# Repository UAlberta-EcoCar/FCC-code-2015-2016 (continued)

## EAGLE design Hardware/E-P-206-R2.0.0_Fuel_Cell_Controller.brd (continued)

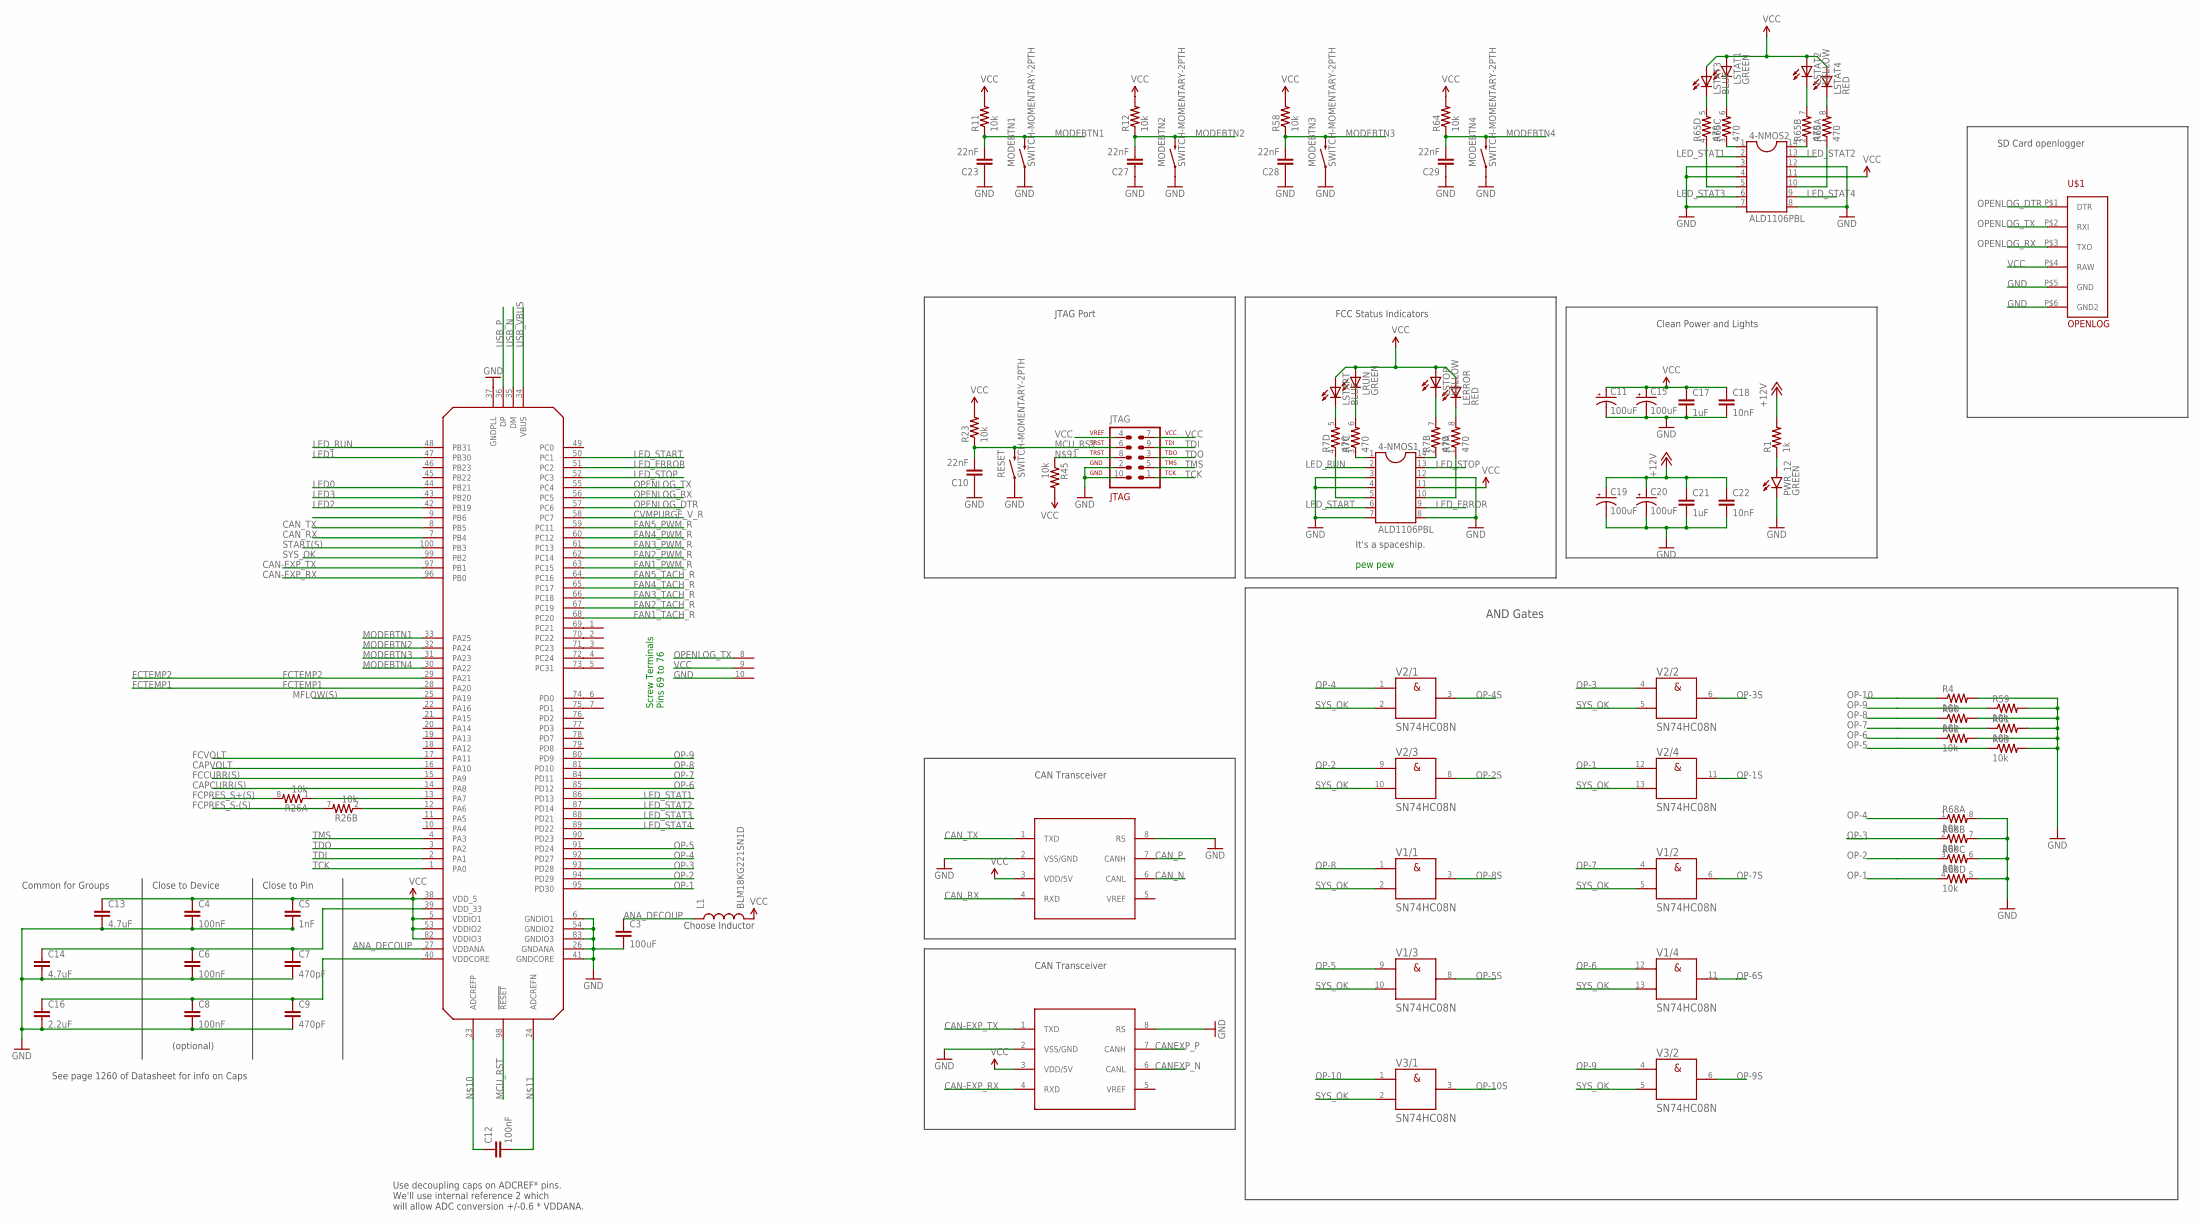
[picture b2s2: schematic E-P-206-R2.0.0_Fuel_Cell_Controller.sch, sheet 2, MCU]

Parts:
4-NMOS1, 4-NMOS2: ALD1106PBL; SOIC-14
C3: 100uF; 0805
C4, C6, C8: 100nF; 0603-CAP
C5: 1nF; 0603-CAP
C7, C9: 470pF; 0603-CAP
C10, C23, C27, C28, C29: 22nF; 0603-CAP
C11, C15, C19, C20: 100uF; PANASONIC_C
C12: 100nF; 0805
C13, C14: 4.7uF; 0805
C16: 2.2uF; 0805
C17, C21: 1uF; 0805
C18, C22: 10nF; 0603-CAP
JTAG: 2x5; AVR-JTAG-10
L1: BLM18KG221SN1D; 0603
LERROR: RED; LED-1206
LRUN: GREEN; LED-1206
LSTART: BLUE; LED-1206
LSTAT1: GREEN; LED-1206
LSTAT2: YELLOW; LED-1206
LSTAT3: BLUE; LED-1206
LSTAT4: RED; LED-1206
LSTOP: YELLOW; LED-1206
MCU: AT32UC3C1512; TQFP100
MODEBTN1, MODEBTN2, MODEBTN3, MODEBTN4: SWITCH-MOMENTARY-2PTH; TACTILE-PTH
PWR_12: GREEN; LED-1206
R1: 1k; 0603-RES
R4, R11, R12, R23, R45, R58, R59, R60, R61, R62, R63, R64: 10k; 0603-RES
R7, R65: 470; 0603-ARV
R26, R68: 10k; 0603-ARV
RESET: SWITCH-MOMENTARY-2PTH; TACTILE-PTH
U$1: OPENLOG
U$2: 10X1PCBBLOCK
U$4, U$36: MCP2551; 8-SOIC
V1, V2, V3: SN74HC08N; DIL14

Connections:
+12V: C19.+, C20.+, C21.1, C22.1, R1.2; also elsewhere on the board
+UB: V1.14 (+UB), V2.14 (+UB), V3.14 (+UB)
-UB: V1.7 (-UB), V2.7 (-UB), V3.7 (-UB)
ANA_DECOUP: C3.1, L1.1, MCU.27 (VDDANA)
CAN-EXP_RX: MCU.96 (PB0), U$36.4 (RXD)
CAN-EXP_TX: MCU.97 (PB1), U$36.1 (TXD)
CANEXP_N: U$36.6 (CANL)
CANEXP_P: U$36.7 (CANH)
CAN_N: U$4.6 (CANL)
CAN_P: U$4.7 (CANH)
CAN_RX: MCU.7 (PB4), U$4.4 (RXD)
CAN_TX: MCU.8 (PB5), U$4.1 (TXD)
CAPCURR(S): MCU.14 (PA8); also elsewhere on the board
CAPVOLT: MCU.16 (PA10); also elsewhere on the board
CVMPURGE_V_R: MCU.58 (PC7); also elsewhere on the board
FAN1_PWM_R: MCU.63 (PC15); also elsewhere on the board
FAN1_TACH_R: MCU.68 (PC20); also elsewhere on the board
FAN2_PWM_R: MCU.62 (PC14); also elsewhere on the board
FAN2_TACH_R: MCU.67 (PC19); also elsewhere on the board
FAN3_PWM_R: MCU.61 (PC13); also elsewhere on the board
FAN3_TACH_R: MCU.66 (PC18); also elsewhere on the board
FAN4_PWM_R: MCU.60 (PC12); also elsewhere on the board
FAN4_TACH_R: MCU.65 (PC17); also elsewhere on the board
FAN5_PWM_R: MCU.59 (PC11); also elsewhere on the board
FAN5_TACH_R: MCU.64 (PC16); also elsewhere on the board
FCCURR(S): MCU.15 (PA9); also elsewhere on the board
FCPRES_S+(S): R26.8 (2); also elsewhere on the board
FCPRES_S-(S): R26.7 (2); also elsewhere on the board
FCTEMP1: MCU.28 (PA20); also elsewhere on the board
FCTEMP2: MCU.29 (PA21); also elsewhere on the board
FCVOLT: MCU.17 (PA11); also elsewhere on the board
GND: 4-NMOS1.3, 4-NMOS1.4, 4-NMOS1.7, 4-NMOS1.8, 4-NMOS1.12, 4-NMOS2.8, 4-NMOS2.12, C3.2, C4.2, C5.2, C6.2, C7.2, C8.2, C9.2, C10.1, C11.-, C13.2, C14.2, C15.-, C16.2, C17.2, C18.2, C19.-, C20.-, C21.2, C22.2, C23.1, C27.1, C28.1, C29.1, JTAG.2, JTAG.10, MCU.6 (GNDIO1), MCU.26 (GNDANA), MCU.37 (GNDPLL), MCU.41 (GNDCORE), MCU.54 (GNDIO2), MCU.83 (GNDIO3), MODEBTN1.1, MODEBTN2.1, MODEBTN3.1, MODEBTN4.1, PWR_12.C, R4.2, R59.2, R60.2, R61.2, R62.2, R63.2, R68.5 (2), R68.6 (2), R68.7 (2), R68.8 (2), RESET.1, U$1.P$5 (GND), U$1.P$6 (GND2), U$2.10, U$4.2 (VSS/GND), U$4.8 (RS), U$36.2 (VSS/GND), U$36.8 (RS); also elsewhere on the board
LED0: MCU.44 (PB21); also elsewhere on the board
LED1: MCU.47 (PB30); also elsewhere on the board
LED2: MCU.42 (PB19); also elsewhere on the board
LED3: MCU.43 (PB20); also elsewhere on the board
LED_ERROR: 4-NMOS1.9, MCU.51 (PC2)
LED_RUN: 4-NMOS1.2, MCU.48 (PB31)
LED_START: 4-NMOS1.6, MCU.50 (PC1)
LED_STAT1: 4-NMOS2.2, MCU.86 (PD13)
LED_STAT2: 4-NMOS2.13, MCU.87 (PD14)
LED_STAT3: 4-NMOS2.3, 4-NMOS2.4, 4-NMOS2.6, 4-NMOS2.7, MCU.88 (PD21)
LED_STAT4: 4-NMOS2.9, MCU.89 (PD22)
LED_STOP: 4-NMOS1.13, MCU.52 (PC3)
MCU_RST: C10.2, JTAG.6, MCU.98 (!RESET), R23.1, RESET.3 (2); also elsewhere on the board
MFLOW(S): MCU.25 (PA19); also elsewhere on the board
MODEBTN1: C23.2, MCU.33 (PA25), MODEBTN1.3 (2), R11.1
MODEBTN2: C27.2, MCU.32 (PA24), MODEBTN2.3 (2), R12.1
MODEBTN3: C28.2, MCU.31 (PA23), MODEBTN3.3 (2), R58.1
MODEBTN4: C29.2, MCU.30 (PA22), MODEBTN4.3 (2), R64.1
unnamed: MCU.12 (PA6), R26.2 (1)
unnamed: MCU.13 (PA7), R26.1
unnamed: C6.1, C7.1, C14.1, MCU.39 (VDD_33)
unnamed: C8.1, C9.1, C16.1, MCU.40 (VDDCORE)
unnamed: C12.1, MCU.23 (ADCREFP)
unnamed: C12.2, MCU.24 (ADCREFN)
unnamed: MCU.69 (PC21), U$2.1
unnamed: MCU.70 (PC22), U$2.2
unnamed: MCU.71 (PC23), U$2.3
unnamed: LSTART.C, R7.5 (2)
unnamed: LRUN.C, R7.6 (2)
unnamed: MCU.72 (PC24), U$2.4
unnamed: MCU.73 (PC31), U$2.5
unnamed: 4-NMOS1.5, R7.4 (1)
unnamed: 4-NMOS1.1, R7.3 (1)
unnamed: PWR_12.A, R1.1
unnamed: MCU.74 (PD0), U$2.6
unnamed: MCU.75 (PD1), U$2.7
unnamed: 4-NMOS2.5, R65.4 (1)
unnamed: 4-NMOS2.1, R65.3 (1)
unnamed: 4-NMOS2.14, R65.2 (1)
unnamed: 4-NMOS2.10, R65.1
unnamed: LSTAT3.C, R65.5 (2)
unnamed: 4-NMOS1.14, R7.2 (1)
unnamed: 4-NMOS1.10, R7.1
unnamed: LSTOP.C, R7.7 (2)
unnamed: LERROR.C, R7.8 (2)
unnamed: LSTAT1.C, R65.6 (2)
unnamed: LSTAT2.C, R65.7 (2)
unnamed: LSTAT4.C, R65.8 (2)
unnamed: JTAG.8, R45.1
OP-1: MCU.95 (PD30), R68.4 (1), V2.12 (A)
OP-1S: V2.11 (Y); also elsewhere on the board
OP-2: MCU.94 (PD29), R68.3 (1), V2.9 (A)
OP-2S: V2.8 (Y); also elsewhere on the board
OP-3: MCU.93 (PD28), R68.2 (1), V2.4 (A)
OP-3S: V2.6 (Y); also elsewhere on the board
OP-4: MCU.92 (PD27), R68.1, V2.1 (A)
OP-4S: V2.3 (Y); also elsewhere on the board
OP-5: MCU.91 (PD24), R63.1, V1.9 (A)
OP-5S: V1.8 (Y); also elsewhere on the board
OP-6: MCU.85 (PD12), R62.1, V1.12 (A)
OP-6S: V1.11 (Y); also elsewhere on the board
OP-7: MCU.84 (PD11), R61.1, V1.4 (A)
OP-7S: V1.6 (Y); also elsewhere on the board
OP-8: MCU.81 (PD10), R60.1, V1.1 (A)
OP-8S: V1.3 (Y); also elsewhere on the board
OP-9: MCU.80 (PD9), R59.1, V3.4 (A)
OP-9S: V3.6 (Y); also elsewhere on the board
OP-10: R4.1, V3.1 (A)
OP-10S: V3.3 (Y); also elsewhere on the board
OPENLOG_DTR: MCU.57 (PC6), U$1.P$1 (DTR)
OPENLOG_RX: MCU.56 (PC5), U$1.P$3 (TXO)
OPENLOG_TX: MCU.55 (PC4), U$1.P$2 (RXI), U$2.8
START(S): MCU.100 (PB3); also elsewhere on the board
SYS_OK: MCU.99 (PB2), V1.2 (B), V1.5 (B), V1.10 (B), V1.13 (B), V2.2 (B), V2.5 (B), V2.10 (B), V2.13 (B), V3.2 (B), V3.5 (B); also elsewhere on the board
TCK: JTAG.1, MCU.1 (PA0)
TDI: JTAG.9, MCU.2 (PA1)
TDO: JTAG.3, MCU.3 (PA2)
TMS: JTAG.5, MCU.4 (PA3)
USB_N: MCU.35 (DM)
USB_P: MCU.36 (DP)
USB_VBUS: MCU.34 (VBUS)
VCC: 4-NMOS1.11, 4-NMOS2.11, C4.1, C5.1, C11.+, C13.1, C15.+, C17.1, C18.1, JTAG.4, JTAG.7, L1.2, LERROR.A, LRUN.A, LSTART.A, LSTAT1.A, LSTAT2.A, LSTAT3.A, LSTAT4.A, LSTOP.A, MCU.5 (VDDIO1), MCU.38 (VDD_5), MCU.53 (VDDIO2), MCU.82 (VDDIO3), R11.2, R12.2, R23.2, R45.2, R58.2, R64.2, U$1.P$4 (RAW), U$2.9, U$4.3 (VDD/5V), U$36.3 (VDD/5V); also elsewhere on the board

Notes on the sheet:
Choose Inductor
Use decoupling caps on ADCREF* pins. We'll use internal reference 2 which will allow ADC conversion +/-0.6 * VDDANA.
Close to Pin
Close to Device
Common for Groups
JTAG Port
(optional)
See page 1260 of Datasheet for info on Caps
CAN Transceiver
Clean Power and Lights
FCC Status Indicators
It's a spaceship.
pew pew
AND Gates
Screw Terminals Pins 69 to 76
SD Card openlogger

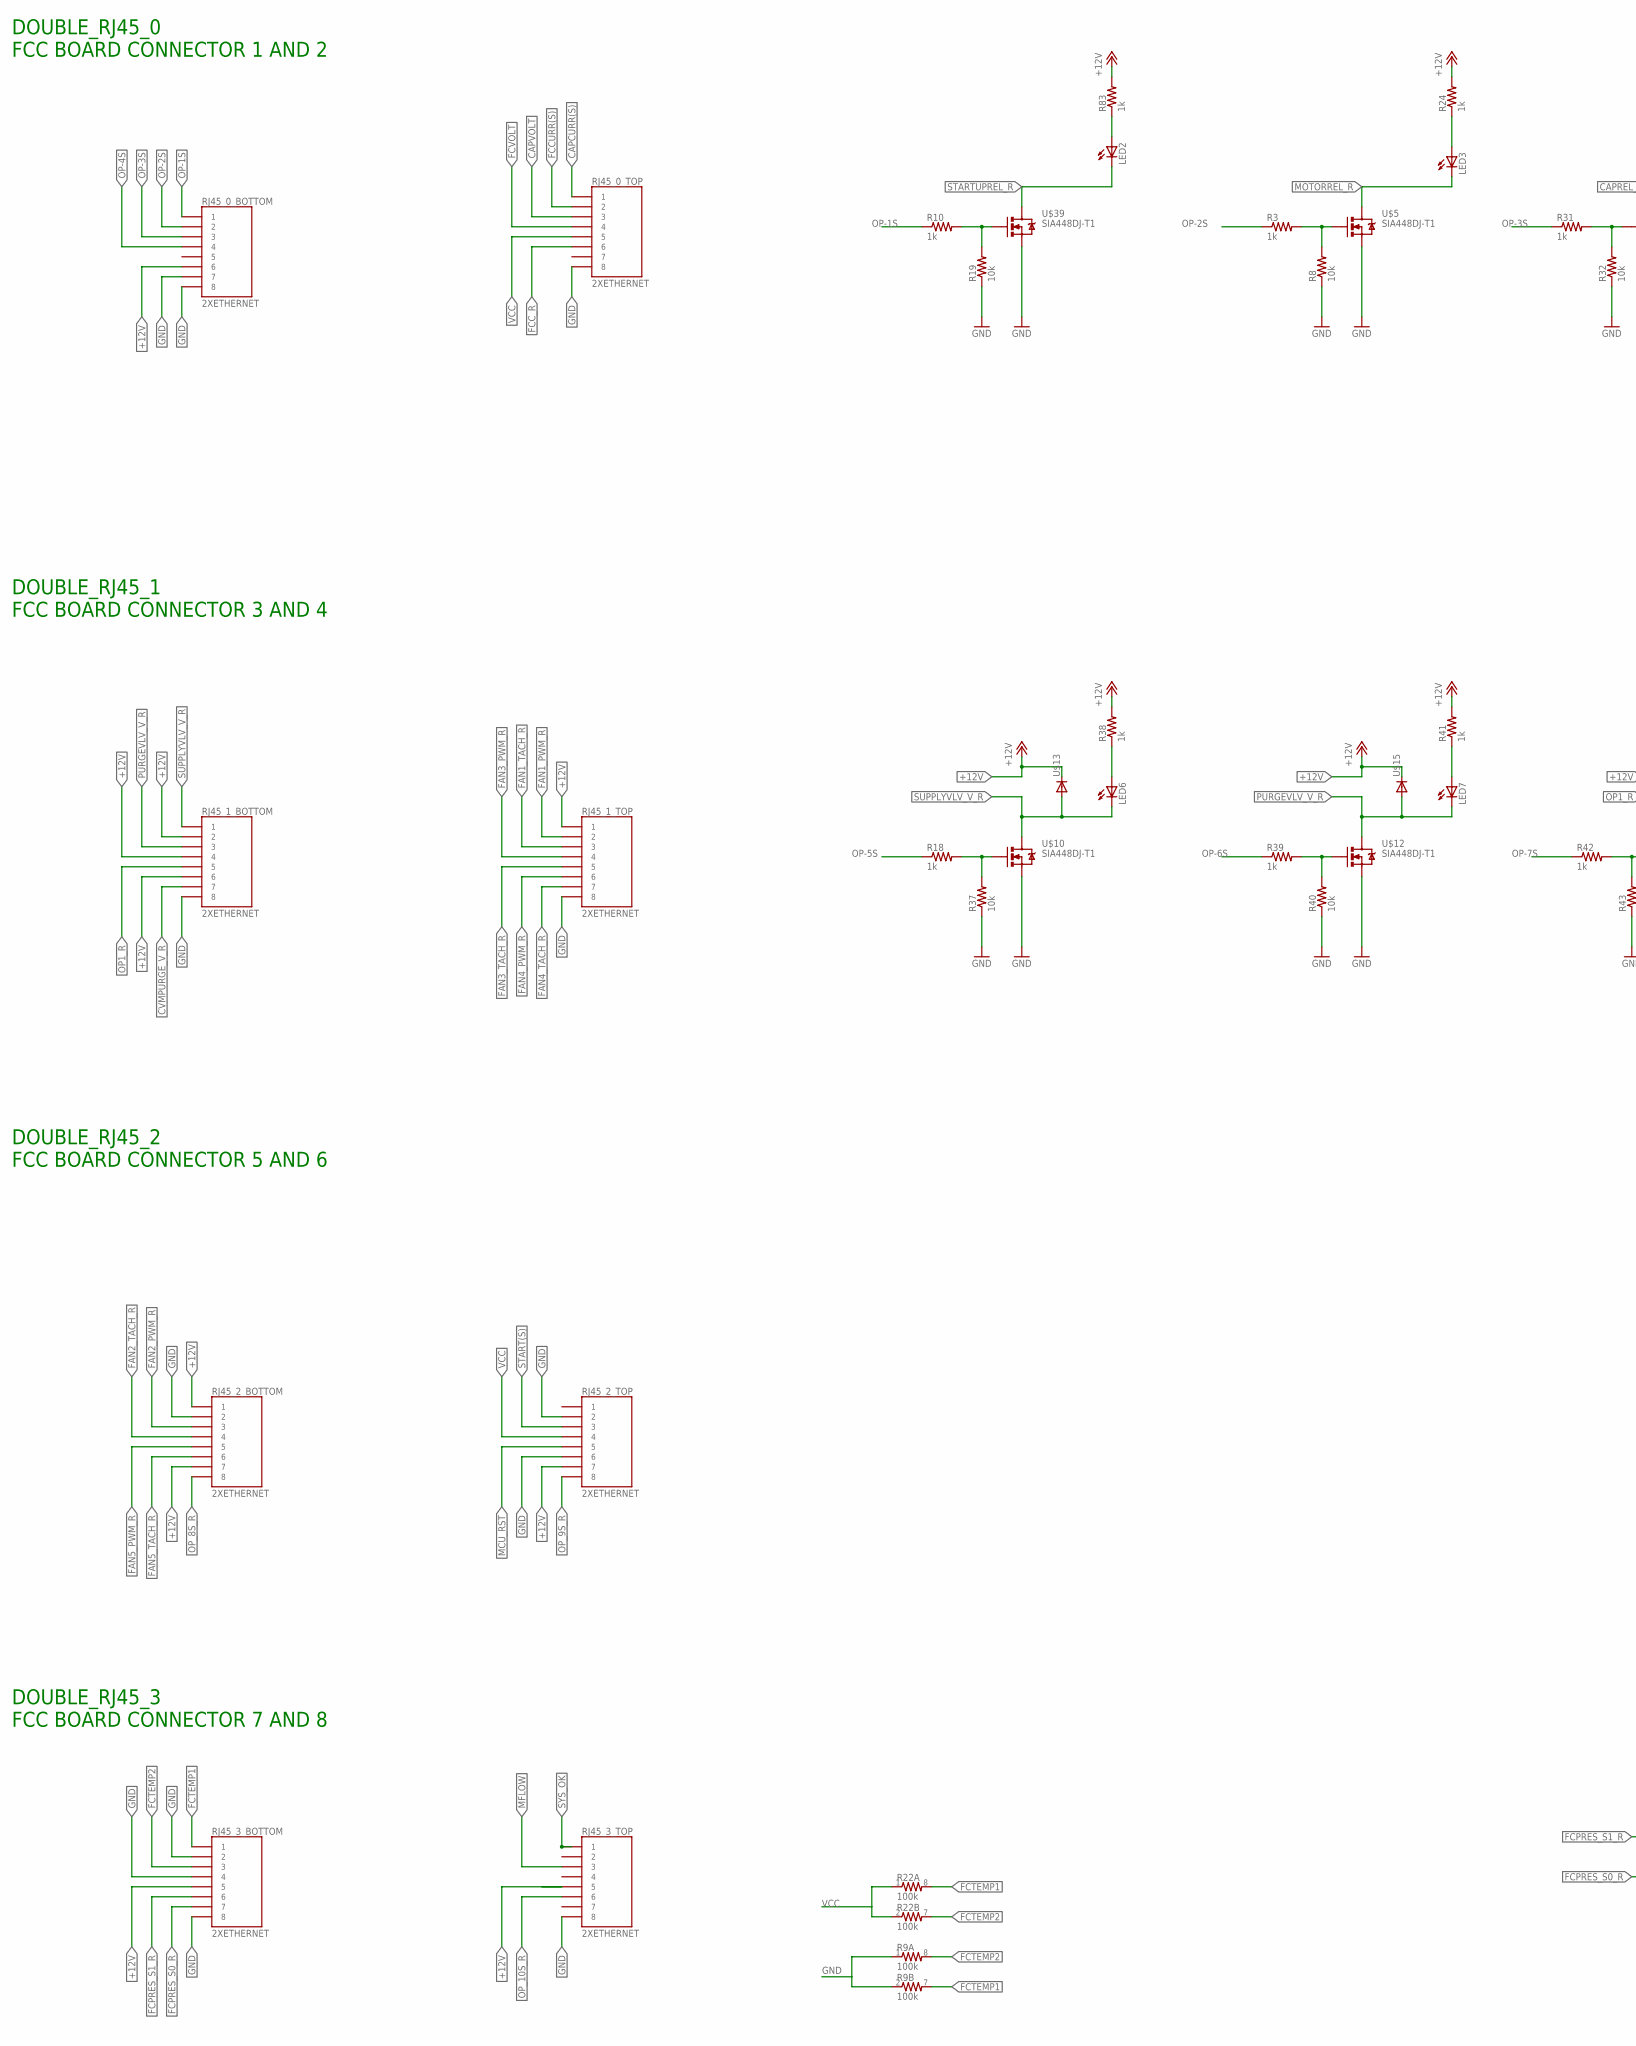
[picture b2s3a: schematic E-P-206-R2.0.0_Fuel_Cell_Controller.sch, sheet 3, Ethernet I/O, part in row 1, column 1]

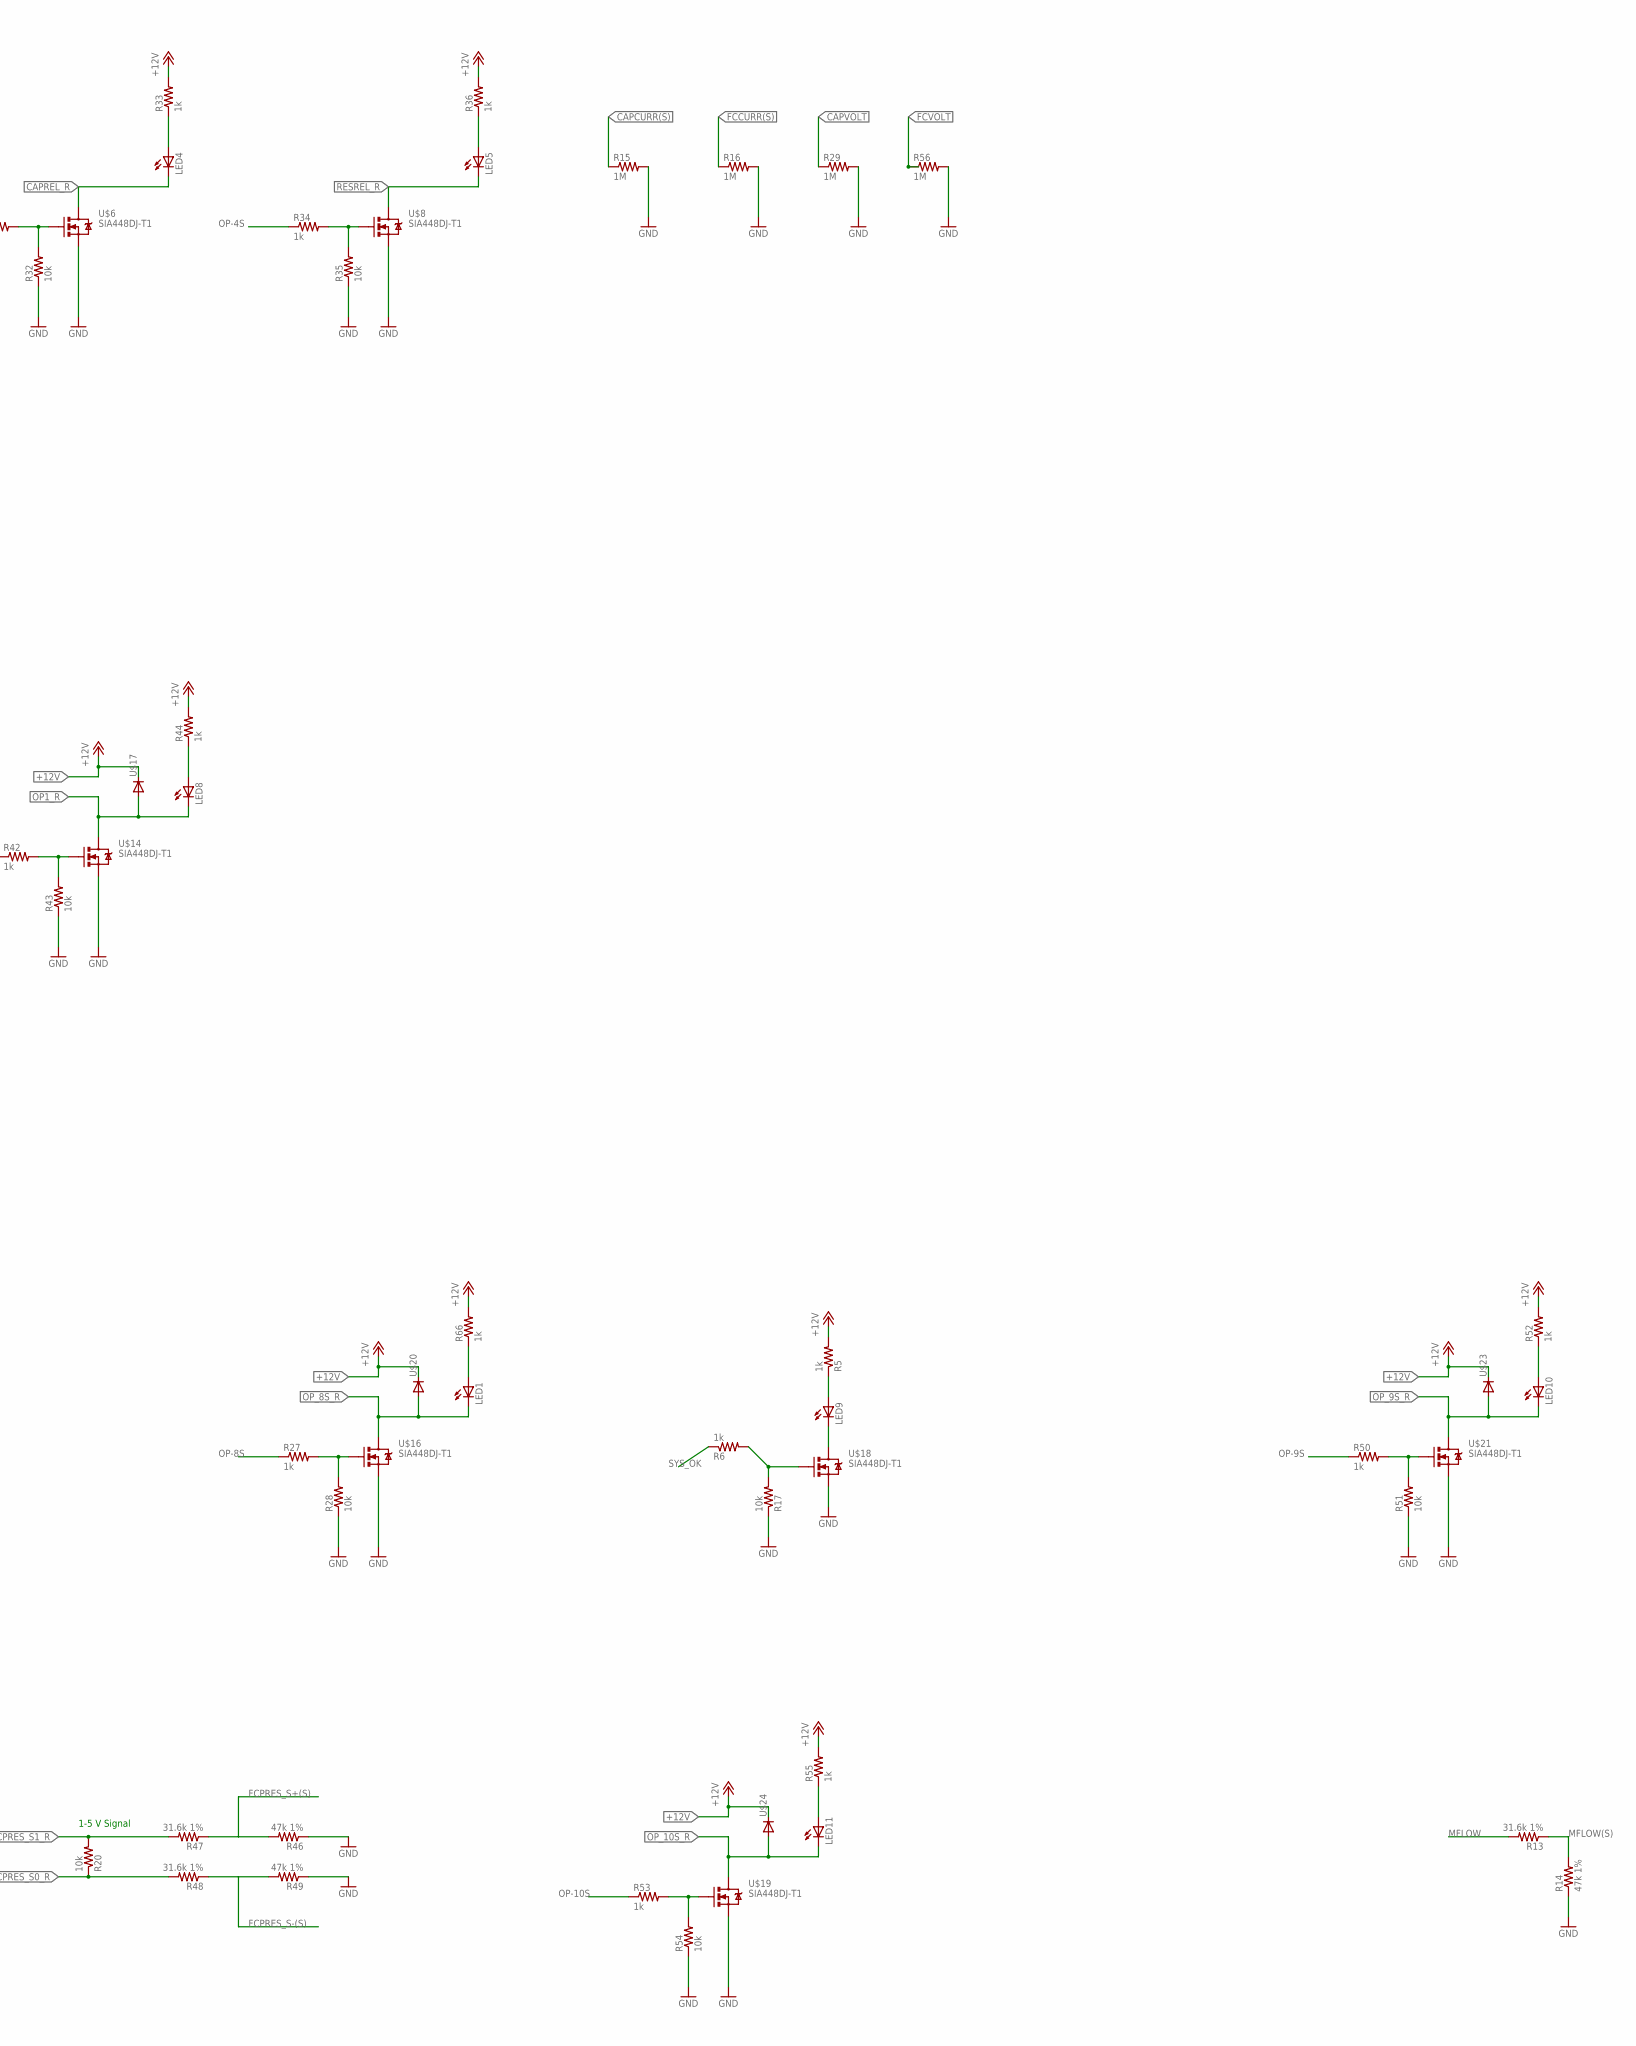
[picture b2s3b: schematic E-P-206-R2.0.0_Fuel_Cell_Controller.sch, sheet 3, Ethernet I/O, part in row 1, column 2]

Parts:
LED1, LED2, LED3, LED4, LED5, LED6, LED7, LED8, LED9, LED10, LED11: LED1206; LED-1206
R3, R5, R6, R10, R18, R24, R27, R31, R33, R34, R36, R38, R39, R41, R42, R44, R50, R52, R53, R55, R66, R83: 1k; 0603-RES
R8, R17, R19, R20, R28, R32, R35, R37, R40, R43, R51, R54: 10k; 0603-RES
R9, R22: 100k; 0603-ARV
R13, R47, R48: 31.6k 1%; 0603-RES
R14, R46, R49: 47k 1%; 0603-RES
R15, R16, R29, R56: 1M; R0805
RJ45_0_, RJ45_1_, RJ45_2_, RJ45_3_: 2XETHERNET
U$5, U$6, U$8, U$10, U$12, U$14, U$16, U$18, U$19, U$21, U$39: SIA448DJ-T1; SC70-6L
U$13, U$15, U$17, U$20, U$23, U$24: DIODE-DO214AC; DO214AC

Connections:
+12V: R5.2, R24.2, R33.2, R36.2, R38.2, R41.2, R44.2, R52.2, R55.2, R66.2, R83.2, RJ45_0_.B_6 (6), RJ45_1_.B_2 (2), RJ45_1_.B_4 (4), RJ45_1_.B_6 (6), RJ45_1_.T_1 (1), RJ45_2_.B_1 (1), RJ45_2_.B_7 (7), RJ45_2_.T_7 (7), RJ45_3_.B_5 (5), RJ45_3_.T_5 (5), U$13.C, U$15.C, U$17.C, U$20.C, U$23.C, U$24.C; also elsewhere on the board
CAPCURR(S): R15.1, RJ45_0_.T_1 (1); also elsewhere on the board
CAPREL_R: LED4.C, U$6.D
CAPVOLT: R29.1, RJ45_0_.T_3 (3); also elsewhere on the board
CVMPURGE_V_R: RJ45_1_.B_7 (7); also elsewhere on the board
FAN1_PWM_R: RJ45_1_.T_2 (2); also elsewhere on the board
FAN1_TACH_R: RJ45_1_.T_3 (3); also elsewhere on the board
FAN2_PWM_R: RJ45_2_.B_3 (3); also elsewhere on the board
FAN2_TACH_R: RJ45_2_.B_4 (4); also elsewhere on the board
FAN3_PWM_R: RJ45_1_.T_4 (4); also elsewhere on the board
FAN3_TACH_R: RJ45_1_.T_5 (5); also elsewhere on the board
FAN4_PWM_R: RJ45_1_.T_6 (6); also elsewhere on the board
FAN4_TACH_R: RJ45_1_.T_7 (7); also elsewhere on the board
FAN5_PWM_R: RJ45_2_.B_5 (5); also elsewhere on the board
FAN5_TACH_R: RJ45_2_.B_6 (6); also elsewhere on the board
FCCURR(S): R16.1, RJ45_0_.T_2 (2); also elsewhere on the board
FCC_R: RJ45_0_.T_6 (6)
FCPRES_S0_R: R20.1, R48.2, RJ45_3_.B_7 (7)
FCPRES_S1_R: R20.2, R47.2, RJ45_3_.B_6 (6)
FCPRES_S+(S): R46.2, R47.1; also elsewhere on the board
FCPRES_S-(S): R48.1, R49.2; also elsewhere on the board
FCTEMP1: R9.7 (2), R22.8 (2), RJ45_3_.B_1 (1); also elsewhere on the board
FCTEMP2: R9.8 (2), R22.7 (2), RJ45_3_.B_3 (3); also elsewhere on the board
FCVOLT: R56.1, RJ45_0_.T_4 (4); also elsewhere on the board
GND: R8.1, R9.1, R9.2 (1), R14.1, R15.2, R16.2, R17.1, R19.1, R28.1, R29.2, R32.1, R35.1, R37.1, R40.1, R43.1, R46.1, R49.1, R51.1, R54.1, R56.2, RJ45_0_.B_7 (7), RJ45_0_.B_8 (8), RJ45_0_.T_8 (8), RJ45_1_.B_8 (8), RJ45_1_.T_8 (8), RJ45_2_.B_2 (2), RJ45_2_.T_2 (2), RJ45_2_.T_6 (6), RJ45_3_.B_2 (2), RJ45_3_.B_4 (4), RJ45_3_.B_8 (8), RJ45_3_.T_8 (8), U$5.S@0 (S), U$5.S@1 (S), U$6.S@0 (S), U$6.S@1 (S), U$8.S@0 (S), U$8.S@1 (S), U$10.S@0 (S), U$10.S@1 (S), U$12.S@0 (S), U$12.S@1 (S), U$14.S@0 (S), U$14.S@1 (S), U$16.S@0 (S), U$16.S@1 (S), U$18.S@0 (S), U$18.S@1 (S), U$19.S@0 (S), U$19.S@1 (S), U$21.S@0 (S), U$21.S@1 (S), U$39.S@0 (S), U$39.S@1 (S); also elsewhere on the board
MCU_RST: RJ45_2_.T_5 (5); also elsewhere on the board
MFLOW: R13.2, RJ45_3_.T_3 (3)
MFLOW(S): R13.1, R14.2; also elsewhere on the board
MOTORREL_R: LED3.C, U$5.D
unnamed: LED9.A, R5.1
unnamed: R10.2, R19.2, U$39.G
unnamed: LED9.C, U$18.D
unnamed: R3.2, R8.2, U$5.G
unnamed: LED2.A, R83.1
unnamed: R31.2, R32.2, U$6.G
unnamed: LED3.A, R24.1
unnamed: R34.2, R35.2, U$8.G
unnamed: LED4.A, R33.1
unnamed: R18.2, R37.2, U$10.G
unnamed: LED5.A, R36.1
unnamed: R27.2, R28.2, U$16.G
unnamed: R39.2, R40.2, U$12.G
unnamed: LED6.A, R38.1
unnamed: R42.2, R43.2, U$14.G
unnamed: LED7.A, R41.1
unnamed: R50.2, R51.2, U$21.G
unnamed: LED8.A, R44.1
unnamed: R53.2, R54.2, U$19.G
unnamed: R6.2, R17.2, U$18.G
unnamed: LED1.A, R66.1
unnamed: LED10.A, R52.1
unnamed: LED11.A, R55.1
OP1_R: LED8.C, RJ45_1_.B_5 (5), U$14.D, U$17.A
OP-1S: R10.1, RJ45_0_.B_1 (1); also elsewhere on the board
OP-2S: R3.1, RJ45_0_.B_2 (2); also elsewhere on the board
OP-3S: R31.1, RJ45_0_.B_3 (3); also elsewhere on the board
OP-4S: R34.1, RJ45_0_.B_4 (4); also elsewhere on the board
OP-5S: R18.1; also elsewhere on the board
OP-6S: R39.1; also elsewhere on the board
OP-7S: R42.1; also elsewhere on the board
OP-8S: R27.1; also elsewhere on the board
OP-9S: R50.1; also elsewhere on the board
OP-10S: R53.1; also elsewhere on the board
OP_8S_R: LED1.C, RJ45_2_.B_8 (8), U$16.D, U$20.A
OP_9S_R: LED10.C, RJ45_2_.T_8 (8), U$21.D, U$23.A
OP_10S_R: LED11.C, RJ45_3_.T_6 (6), U$19.D, U$24.A
PURGEVLV_V_R: LED7.C, RJ45_1_.B_3 (3), U$12.D, U$15.A
RESREL_R: LED5.C, U$8.D
START(S): RJ45_2_.T_3 (3); also elsewhere on the board
STARTUPREL_R: LED2.C, U$39.D
SUPPLYVLV_V_R: LED6.C, RJ45_1_.B_1 (1), U$10.D, U$13.A
SYS_OK: R6.1, RJ45_3_.T_1 (1); also elsewhere on the board
VCC: R22.1, R22.2 (1), RJ45_0_.T_5 (5), RJ45_2_.T_4 (4); also elsewhere on the board

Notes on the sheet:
DOUBLE_RJ45_0 FCC BOARD CONNECTOR 1 AND 2
DOUBLE_RJ45_1 FCC BOARD CONNECTOR 3 AND 4
DOUBLE_RJ45_2 FCC BOARD CONNECTOR 5 AND 6
DOUBLE_RJ45_3 FCC BOARD CONNECTOR 7 AND 8
1-5 V Signal

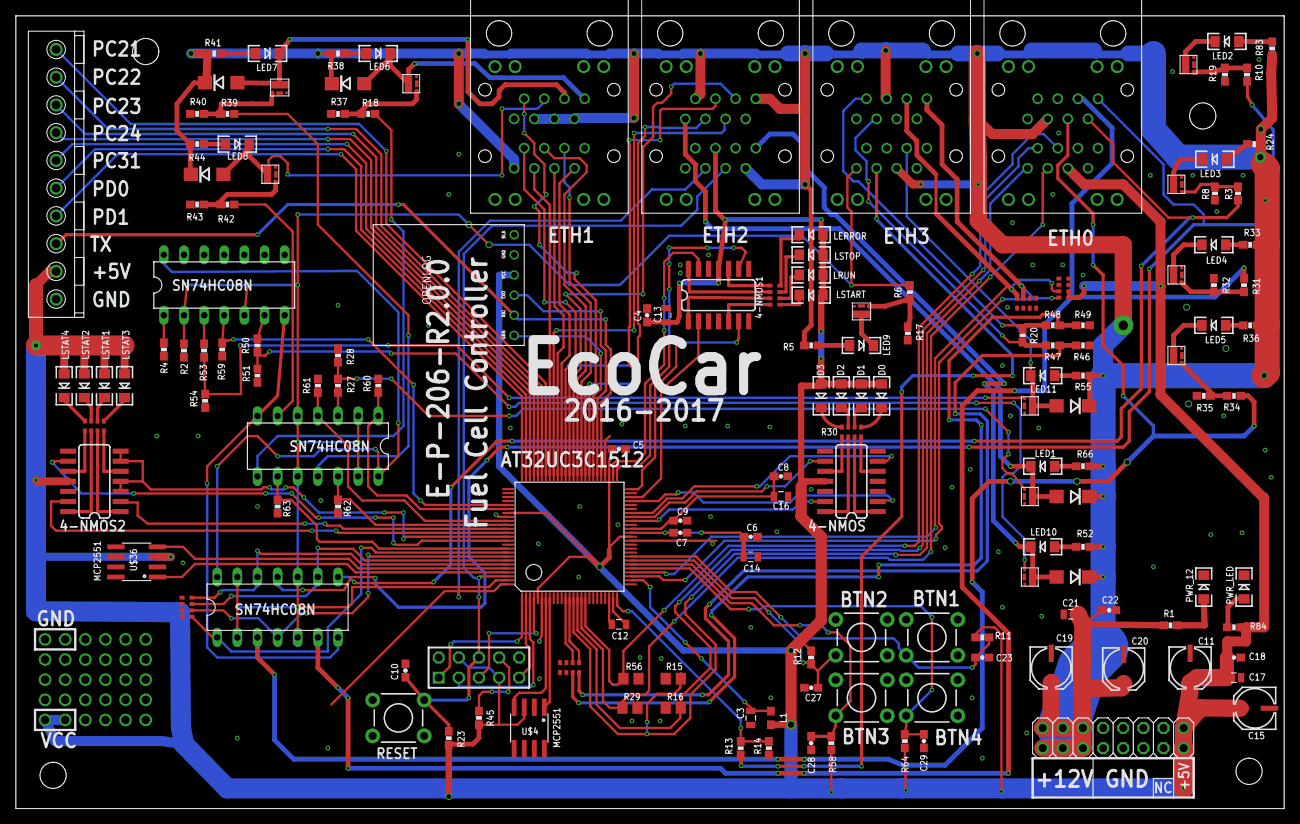
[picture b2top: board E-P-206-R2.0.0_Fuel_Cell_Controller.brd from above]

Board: 2 copper layers, 160.0 x 100.0 mm, 159 parts (0 on the bottom side), 152 nets.

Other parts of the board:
U$3, U$22, U$25, U$27: STAND-OFF

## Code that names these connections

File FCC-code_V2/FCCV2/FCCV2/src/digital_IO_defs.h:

/*
 * IncFile1.h
 *
 * Created: 2015-10-10 1:47:04 PM
 *  Author: Reegan
 */ 
#ifndef FUELCELL_IO_H
#define FUELCELL_IO_H
//digital Inputs
#define MODEBTN1 AVR32_PIN_PA25
#define MODEBTN2 AVR32_PIN_PA24
#define MODEBTN3 AVR32_PIN_PA23
#define MODEBTN4 AVR32_PIN_PA22
#define FAN5_TACH_R AVR32_PIN_PC16
#define CVM_PROBE_DISCONNECT AVR32_PIN_PC17
#define FAN3_TACH_R AVR32_PIN_PC18
#define FAN2_TACH_R AVR32_PIN_PC19
#define FAN1_TACH_R AVR32_PIN_PC20
#define CVM_PURGE_V_R AVR32_PIN_PC07
#define START AVR32_PIN_PB03
#define SYSOK AVR32_PIN_PB02
//PB23 unused
//PC00 unused
//PB22 unused
//PD02 unused
//PC06 unused
//LEDs
#define LED0 AVR32_PIN_PB21
#define LED1 AVR32_PIN_PB30
#define LED2 AVR32_PIN_PB19
#define LED3 AVR32_PIN_PB20
#define LED_RUN AVR32_PIN_PB31
#define LED_START AVR32_PIN_PC01
#define LED_ERROR AVR32_PIN_PC02
#define LED_STOP AVR32_PIN_PC03
#define LED_STAT1 AVR32_PIN_PD13
#define LED_STAT2 AVR32_PIN_PD14
#define LED_STAT3 AVR32_PIN_PD21
#define LED_STAT4 AVR32_PIN_PD22
//Coil driving outputs
#define OP_1 AVR32_PIN_PD30
#define OP_2 AVR32_PIN_PD29
#define OP_3 AVR32_PIN_PD28
#define OP_4 AVR32_PIN_PD27
#define OP_5 AVR32_PIN_PD24
#define OP_6 AVR32_PIN_PD12
#define OP_7 AVR32_PIN_PD11
#define OP_8 AVR32_PIN_PD10
#define OP_9 AVR32_PIN_PD09
//PD08 unused
//digital outputs
//relays
#define START_RELAY OP_1
#define RES_RELAY OP_4
#define CAP_RELAY OP_3
#define MOTOR_RELAY OP_2
//valves
#define PURGE_VALVE OP_6
#define H2_VALVE OP_5
#endif /* INCFILE1_H_ */

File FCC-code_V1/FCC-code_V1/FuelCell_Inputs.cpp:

#include "FuelCell_Inputs.h"
#include <avr32/io.h>
#include "myADC.h"

void InputsInit (void)
{
	//set DDR for all inputs
	//page 11 of datasheet needed
	
	
	//set analog inputs
	SetAsAnalogIn(1,5); //set PA5 as ADCIN1
	SetAsAnalogIn(1,7); //set PA7 as ADCIN3
	SetAsAnalogIn(1,8); //set PA8 as ADCIN4
	SetAsAnalogIn(1,9); //set PA9 as ADCIN5
	SetAsAnalogIn(1,10); //set PA10 as ADCIN6
	SetAsAnalogIn(1,11); //set PA11 as ADCIN7
	//maybe set up interrupts
	
	//set up ADC
	ADCInit();
}

unsigned char ReadSTART(void)
{
	//The START signal tiggers the Fuel Cell Controller
	//to go into its startup mode
	//Connected to PB3 = GPIO port 2 pin 3
	if(AVR32_GPIO.port[1].pvr & (1 << 3))
	{
		return(1);
	}
	return(0); 
}

unsigned char ReadSYSOK(void)
{
	//The SYSOK signal indicates that the system 
	//is in proper operating condition. 
	//It should be shorted to ground in case of an 
	//emergency stop event such as an emergency 
	//stop button press, or unsafe hydrogen level.
	//Connected to PB2
	if(AVR32_GPIO.port[1].pvr & (1 << 2))
	{
		return(1);
	}
	return(0); 
}

unsigned int ReadTANKPRES(void)
{
	//The TANKPRES signal indicates the pressure 
	//in the line from the hydrogen tank.	
	//S- PA4 unused. Analog input
	//PA5 Attached to S- with 10k res. Analog input
	
	//ADCIN1
	//using sequencer 0
	AVR32_ADCIFA.inpsel00 = 1; //conversion 1, adcin1, seq 0. see page 1146 of datasheet	
	AVR32_ADCIFA.innsel00 = 9; //select ground as neg ref
	return(AnalogRead(0));
}

unsigned int ReadFCPRES(void)
{
	//The FCPRES signal indicates the hydrogen pressure 
	//at the input to the fuel cell.
	//PA6 unused
	//PA7 Analog input
	AVR32_ADCIFA.inpsel00 = 3; //conversion 1, adcin3, seq 0. see page 1146 of datasheet
	AVR32_ADCIFA.innsel00 = 9; //select ground as neg ref
	return(AnalogRead(0));
}

unsigned int ReadFAN_TAC(void)
{
	//PD2. Fan Tachometer
	return(0); //to remove compiler warning
}

unsigned int ReadFCCURR(void)
{
	//The FCCUR current sensor reports the current flowing from the fuel cell	
	//PA9 Analog input
	AVR32_ADCIFA.inpsel00 = 5; //conversion 1, adcin5, seq 0. see page 1146 of datasheet
	AVR32_ADCIFA.innsel00 = 9; //select ground as neg ref
	return(AnalogRead(0));
}

unsigned int ReadFCVOLT(void)
{
	//Reads fuel cell voltage. voltage divider
	//PA11
	AVR32_ADCIFA.inpsel00 = 7; //conversion 1, adcin 7, seq 0. see page 1146 of data sheet
	AVR32_ADCIFA.innsel00 = 9; //select ground as neg ref
	return(AnalogRead(0));
}


unsigned char ReadFCCON(void)
{
	//determines if the fuel cell is connected
	//PB23 = GPIO port 1 pin 23
	if(AVR32_GPIO.port[1].pvr & (1 << 23))
	{
		return(1);
	}
	return(0);
}

unsigned int ReadCAPCURR(void)
{
	//The CAPCUR current sensor reports the current flowing unsigned into or out of the ultra capacitors.
	//PA8 Analog input
	AVR32_ADCIFA.inpsel00 = 4; //conversion 1, adcin 4, seq 0. see page 1146 of data sheet
	AVR32_ADCIFA.innsel00 = 9; //select ground as neg ref
	return(AnalogRead(0));
}

unsigned char ReadCAPCON(void)
{
	//determines if the ultra capacitors are connected
	//PC0 = GPIO port 3 pin 0
	/*
	if(AVR32_GPIO.port[2].pvr & 1)
	{
		return(1);
	}
	*/
	
	//has been rewired to PC12
	// = GPIO port 2 pin 12
	if(AVR32_GPIO.port[2].pvr & (1 << 12))
	{
		return(1);
	}
	return(0);
}

unsigned int ReadCAPVOLT(void)
{
	//read the ultra capacitor voltage
	//PA10
	AVR32_ADCIFA.inpsel00 = 6; //conv 1, seq 0, adin6
	AVR32_ADCIFA.innsel00 = 9; //select ground as neg ref
	return(AnalogRead(0));
}

unsigned char ReadRESCON(void)
{
	//determines if the start-up power resistors are connected
	//PB22 = GPIO port 2 pin 22
	if(AVR32_GPIO.port[1].pvr & (1 << 22))
	{
		return(1);
	}
	return(0);
}

unsigned int ReadAMBTEMP1(void)
{
	//PA22
	//this is goofy b/c it is a negative analog input
	AVR32_ADCIFA.inpsel00 = 10; //ground as positive ref
	AVR32_ADCIFA.innsel00 = 3; //conversion 1 adcin 11 = adcinn 3, seq 0
	return(AnalogRead(0)); 
}

unsigned int ReadAMBTEMP2(void)
{
	//PA23
	AVR32_ADCIFA.inpsel00 = 10; //ground as positive ref
	AVR32_ADCIFA.innsel00 = 4; //conversion 1, adcin 12, seq 0
	return(AnalogRead(0)); 
}

unsigned int ReadAMBTEMP3(void)
{
	//PA24
	AVR32_ADCIFA.inpsel00 = 10; //ground as positive ref
	AVR32_ADCIFA.innsel00 = 5; //conversion 1, adcin 13, seq 0
	return(AnalogRead(0));
}

unsigned int ReadAMBTEMP4(void)
{
	//PA25
	AVR32_ADCIFA.inpsel00 = 10; //ground as positive ref
	AVR32_ADCIFA.innsel00 = 6; //conversion 1, adcin 14, seq 0
	return(AnalogRead(0));
}

unsigned int ReadFCTEMP1(void)
{
	//PA20
	AVR32_ADCIFA.inpsel00 = 10; //ground as positive ref
	AVR32_ADCIFA.innsel00 = 1; //conversion 1, adcin 9, seq 0
	return(AnalogRead(0)); 
}

unsigned int ReadFCTEMP2(void)
{
	//PA21
	AVR32_ADCIFA.inpsel00 = 10; //ground as positive ref
	AVR32_ADCIFA.innsel00 = 2; //conversion 1, adcin 10, seq 0
	return(AnalogRead(0));
}

unsigned int ReadMFLOW(void)
{
	//PA19
	AVR32_ADCIFA.inpsel00 = 10; //ground as positive ref
	AVR32_ADCIFA.innsel00 = 0; //conv 1, adcin 8, seq 0
	return(AnalogRead(0));
}

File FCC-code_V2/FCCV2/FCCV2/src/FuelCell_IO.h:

/*
 * IncFile1.h
 *
 * Created: 2015-10-10 1:47:04 PM
 *  Author: Reegan
 */ 


#ifndef FUELCELL_IO_H
#define FUELCELL_IO_H


#define OP1_FAN 0x00000004



//Analog Inputs
#define AMBTEMP4 AVR32_ADCIN14_PIN
#define AMBTEMP3 AVR32_ADCIN13_PIN
#define AMBTEMP2 AVR32_ADCIN12_PIN
#define AMBTEMP1 AVR32_ADCIN11_PIN
#define FCTEMP2 AVR32_ADCIN10_PIN
#define FCTEMP1 AVR32_ADCIN9_PIN
#define MFLOW AVR32_ADCIN8_PIN
#define FCVOLT AVR32_ADCIN7_PIN
#define CAPVOLT AVR32_ADCIN6_PIN
#define FCCURR AVR32_ADCIN5_PIN
#define CAPCURR AVR32_ADCIN4_PIN
#define FCPRES AVR32_ADCIN3_PIN
//adcin2 unused
#define TANKPRES AVR32_ADCIN1_PIN
//adcin0 unused

//Analog GPIO MAP
static const gpio_map_t ADCIFA_GPIO_MAP =
{
	{AMBTEMP4,AVR32_ADCIN14_FUNCTION},
	{AMBTEMP3,AVR32_ADCIN13_FUNCTION},
	{AMBTEMP2,AVR32_ADCIN12_FUNCTION},
	{AMBTEMP1,AVR32_ADCIN11_FUNCTION},
	{FCTEMP2,AVR32_ADCIN10_FUNCTION},
	{FCTEMP1,AVR32_ADCIN9_FUNCTION},
	{MFLOW,AVR32_ADCIN8_FUNCTION},
	{FCVOLT,AVR32_ADCIN7_FUNCTION),
	{CAPVOLT,AVR32_ADCIN6_FUNCTION};
	{FCCURR,AVR32_ADCIN5_FUNCTION};
	{CAPCURR,AVR32_ADCIN4_FUNCTION};
	{FCPRES,AVR32_ADCIN3_FUNCTION};
	{TANKPRES,AVR32_ADCIN1_FUNCTION};
};

//ADC settings
adcifa_opt_t adcifa_opt = {
	.frequency                = 10000,  // ADC frequency (Hz)
	.reference_source         = ADCIFA_REF1V, // Reference Source
	.sample_and_hold_disable  = FALSE,    // Disable Sample and Hold Time
	.single_sequencer_mode    = FALSE,    // Single Sequencer Mode
	.free_running_mode_enable = FALSE,    // Free Running Mode
	.sleep_mode_enable        = FALSE     // Sleep Mode
};

adcifa_sequencer_opt_t adcifa_sequence_opt = {
	.convnb               = 7, // Number of sequence
	.resolution           = ADCIFA_SRES_12B,         // Resolution selection
	.trigger_selection    = ADCIFA_TRGSEL_SOFT,      // Trigger selection
	.start_of_conversion  = ADCIFA_SOCB_ALLSEQ,      // Conversion Management
	.half_word_adjustment = ADCIFA_HWLA_NOADJ,       // Half word Adjustment
	.software_acknowledge = ADCIFA_SA_NO_EOS_SOFTACK // Software Acknowledge
};

adcifa_sequencer_conversion_opt_t adcifa_sequence_conversion_option_0[7] =
{
	{
		.channel_p = AVR32_ADCIFA_INP_GNDANA,   // Positive Channel
		.channel_n = AVR32_ADCIFA_INN_ADCIN8,   // Negative Channel
		.gain      = ADCIFA_SHG_1                     // Gain of the conversion
	},
	{
		.channel_p = AVR32_ADCIFA_INP_GNDANA,             // Positive Channel
		.channel_n = AVR32_ADCIFA_INN_ADCIN9,             // Negative Channel
		.gain      = ADCIFA_SHG_1                     // Gain of the conversion
	},
	{
		.channel_p = AVR32_ADCIFA_INP_GNDANA,             // Positive Channel
		.channel_n = AVR32_ADCIFA_INN_ADCIN10,             // Negative Channel
		.gain      = ADCIFA_SHG_1                     // Gain of the conversion
	},
	{
		.channel_p = AVR32_ADCIFA_INP_GNDANA,             // Positive Channel
		.channel_n = AVR32_ADCIFA_INN_ADCIN11,             // Negative Channel
		.gain      = ADCIFA_SHG_1                     // Gain of the conversion
	},
	{
		.channel_p = AVR32_ADCIFA_INP_GNDANA,             // Positive Channel
		.channel_n = AVR32_ADCIFA_INN_ADCIN12,             // Negative Channel
		.gain      = ADCIFA_SHG_1                     // Gain of the conversion
	},
	{
		.channel_p = AVR32_ADCIFA_INP_GNDANA,             // Positive Channel
		.channel_n = AVR32_ADCIFA_INN_ADCIN13,             // Negative Channel
		.gain      = ADCIFA_SHG_1                     // Gain of the conversion
	},
	{
		.channel_p = AVR32_ADCIFA_INP_GNDANA,             // Positive Channel
		.channel_n = AVR32_ADCIFA_INN_ADCIN14,             // Negative Channel
		.gain      = ADCIFA_SHG_1                     // Gain of the conversion
	},
};

//these are based off of the above sequence order
#define MFLOWValue adcvals_0[0] //sequencer 0 adcin8
#define FCTEMP1Value adcvals_0[1] //seq 0 adcin9
#define FCTEMP2Value adcvals_0[2] //seq 0 adcin10
#define AMBTEMP1Value adcvals_0[3] //seq 0 adcin11
#define AMBTEMP2Value adcvals_0[4] //seq 0 adcin12
#define AMBTEMP3Value adcvals_0[5] //seq 0 adcin13
#define AMBTEMP0Value adcvals_0[6] //seq 0 adcin 14

adcifa_sequencer_conversion_opt_t adcifa_sequence_conversion_option_1[6] =
{
	{
		.channel_p = AVR32_ADCIFA_INP_ADCIN1,             // Positive Channel
		.channel_n = AVR32_ADCIFA_INN_GNDANA,             // Negative Channel
		.gain      = ADCIFA_SHG_1                     // Gain of the conversion
	},
	{
		.channel_p = AVR32_ADCIFA_INP_ADCIN3,             // Positive Channel
		.channel_n = AVR32_ADCIFA_INN_GNDANA,             // Negative Channel
		.gain      = ADCIFA_SHG_1                     // Gain of the conversion
	},
	{
		.channel_p = AVR32_ADCIFA_INP_ADCIN4,             // Positive Channel
		.channel_n = AVR32_ADCIFA_INN_GNDANA,             // Negative Channel
		.gain      = ADCIFA_SHG_1                     // Gain of the conversion
	},
	{
		.channel_p = AVR32_ADCIFA_INP_ADCIN5,             // Positive Channel
		.channel_n = AVR32_ADCIFA_INN_GNDANA,             // Negative Channel
		.gain      = ADCIFA_SHG_1                     // Gain of the conversion
	},
	{
		.channel_p = AVR32_ADCIFA_INP_ADCIN6,             // Positive Channel
		.channel_n = AVR32_ADCIFA_INN_GNDANA,             // Negative Channel
		.gain      = ADCIFA_SHG_1                     // Gain of the conversion
	},
	{
		.channel_p = AVR32_ADCIFA_INP_ADCIN7,             // Positive Channel
		.channel_n = AVR32_ADCIFA_INN_GNDANA,             // Negative Channel
		.gain      = ADCIFA_SHG_1                     // Gain of the conversion
	},
};

//these are based off the above sequencer order
#define TANKPRESValue adcvals_1[0] //seq 1 adcin1
#define FCPRESValue adcvals_1[1] //seq 1 adcin3
#define CAPCURRValue adcvals_1[2] //seq 1 adcin4
#define FCCURRValue adcvals_1[3] //seq 1 adcin5
#define CAPVOLTValue adcvals_1[4] //seq 1 adcin6
#define FCVOLTValue adcvals_1[5] //seq 1 adcin7


//digital Inputs
#define START AVR32_PIN_PB03
#define SYSOK AVR32_PIN_PB02
#define FCCON AVR32_PIN_PB23
#define CAPCON AVR32_PIN_PC00
#define RESCON AVR32_PIN_PB22

//LEDs
#define LED0 AVR32_PIN_PB21
#define LED1 AVR32_PIN_PB30
#define LED2 AVR32_PIN_PB19
#define LED3 AVR32_PIN_PB20
#define LED_RUN AVR32_PIN_PB31
#define LED_START AVR32_PIN_PC01
#define LED_ERROR AVR32_PIN_PC02
#define LED_STOP AVR32_PIN_PC03

//Coil driving outputs
#define OP_1 AVR32_PIN_PD30
#define OP_2 AVR32_PIN_PD29
#define OP_3 AVR32_PIN_PD28
#define OP_4 AVR32_PIN_PD27
#define OP_5 AVR32_PIN_PD24
#define OP_6 AVR32_PIN_PD12
#define OP_7 AVR32_PIN_PD11
#define OP_8 AVR32_PIN_PD10
#define OP_9 AVR32_PIN_PD09
#define OP_10 AVR32_PIN_PD08


#endif /* INCFILE1_H_ */
